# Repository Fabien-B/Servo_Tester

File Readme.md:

Servo Tester
=============

_This project is a work in progress. Some features are missing._

A device to quickly command servomoteurs and other stuff like I2C or CAN devices.

Based on a nucleo32 L432KC, this device allow to command up to 5 (only 3 working for now) classic servomotors.
It also support dynamixel AX-12A servomotors.

## Hardware

PCB was made with Kicad 5.0. Go to the Release page to get the gerbers files.

Run `git submodule update --init --recursive` to fetch kicad libraries.

## Software

The embedded firware uses ChibiOs.

For instructions about embedded firmware go to the appropriate [Readme file](software/embedded/Readme.md).

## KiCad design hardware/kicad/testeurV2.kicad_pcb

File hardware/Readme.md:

Tester hardware
================

The jumpers configuration on the NUCLEO L432KC needs to be changed: remove SB18, SB16 (for the I2C) and SB9 (to allow powering through 5V pin).

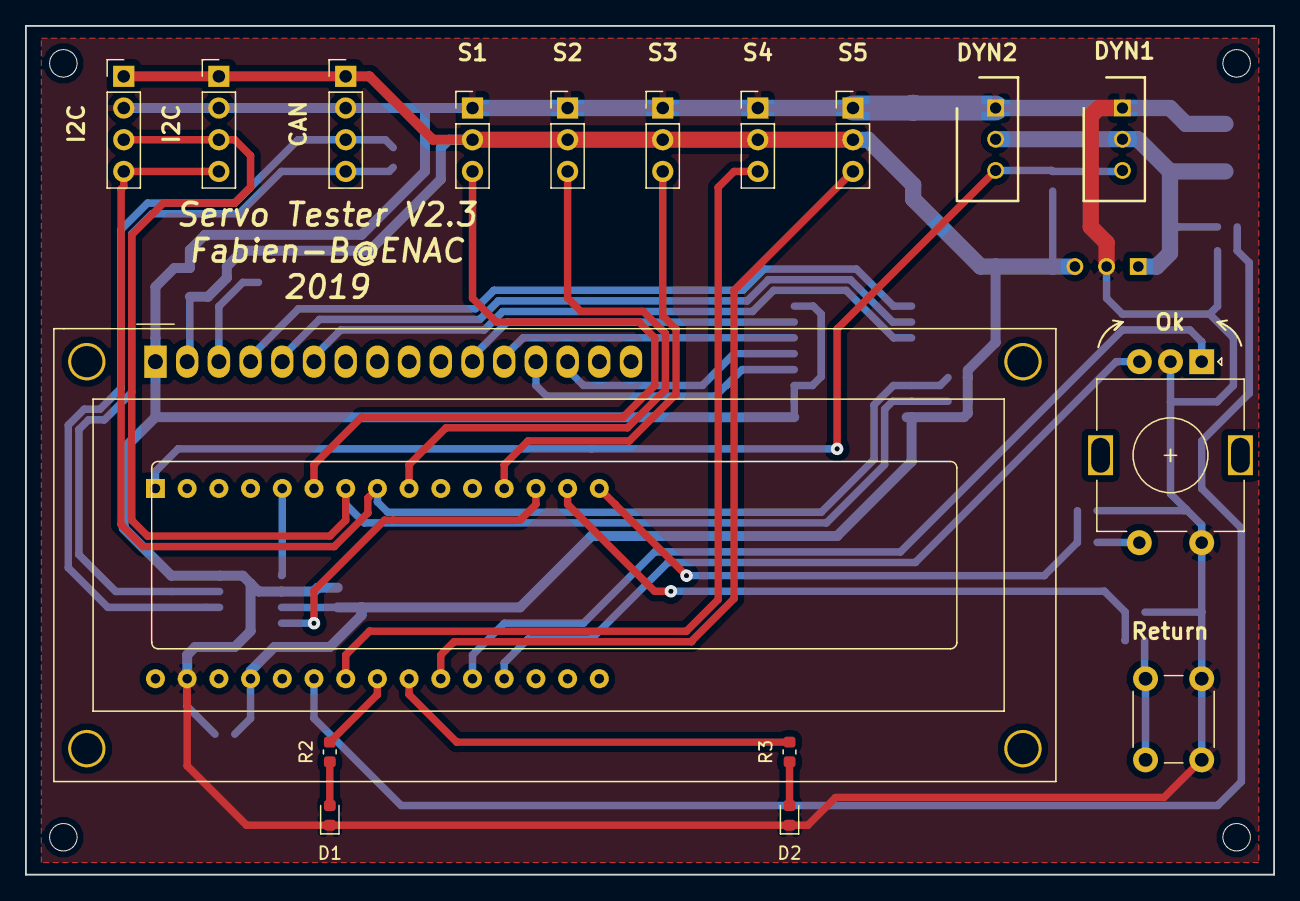
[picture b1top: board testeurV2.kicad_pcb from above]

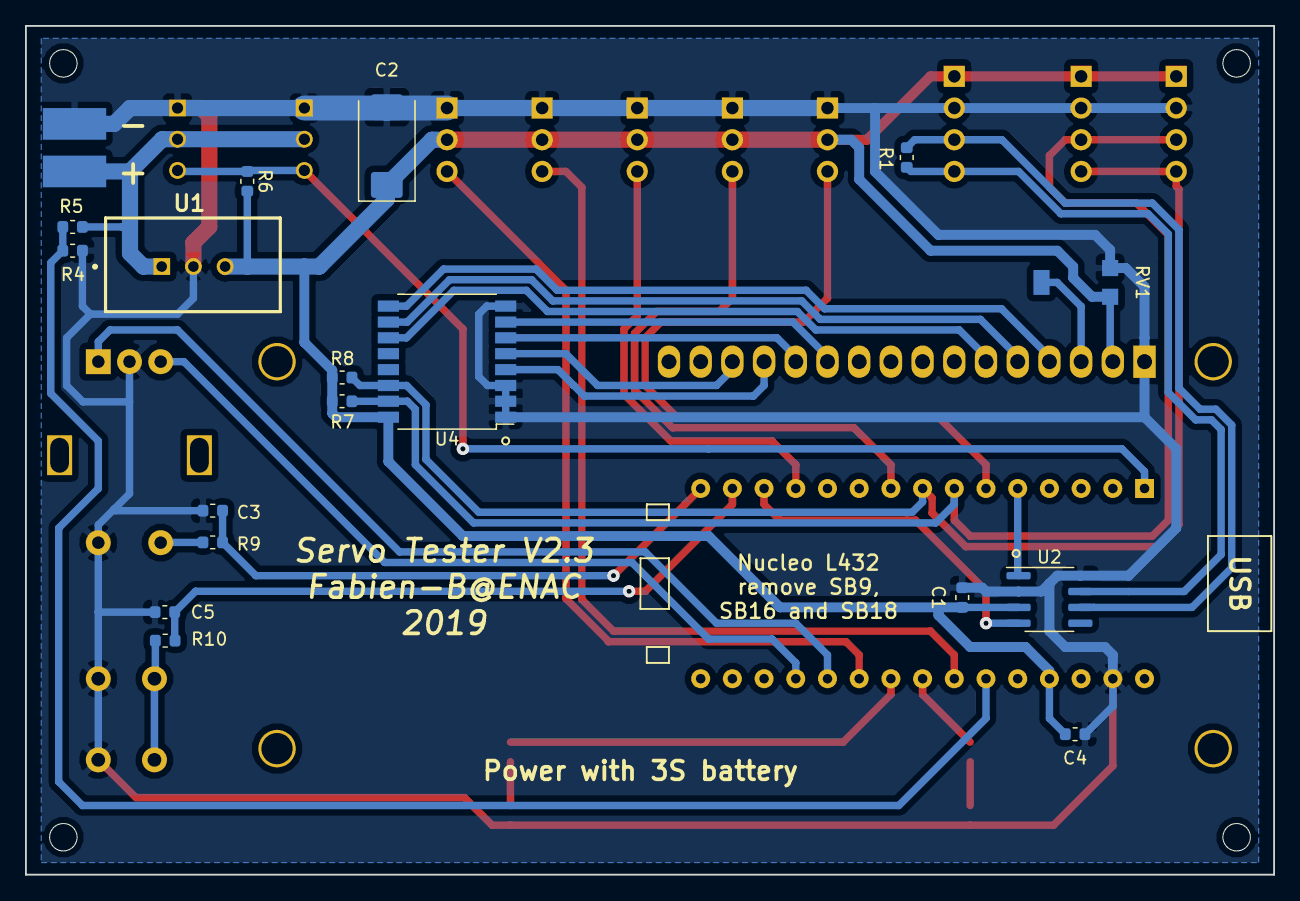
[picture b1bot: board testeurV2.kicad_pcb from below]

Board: 2 copper layers, 100.0 x 68.0 mm, 36 parts (19 on the bottom side), 34 nets.

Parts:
C1, C4: 100nF; C_0603_1608Metric
C2: 100µF; CP_EIA-7343-31_Kemet-D
C3, C5: 330nF; C_0603_1608Metric
CAN1: J_01x04P2.54; PinHeader_1x04_P2.54mm_Vertical
D1, D2: LED; LED_0603_1608Metric
DS1: WC1602A
DYN1, DYN2: 22-03-5035; SHDR3W70P0X250_1X3_990X490X590P
I2C1_a1, I2C1_b1: J_01x04P2.54; PinHeader_1x04_P2.54mm_Vertical
OK1: Rotary_Encoder_Switch; RotaryEncoder_Alps_EC11E-Switch_Vertical_H20mm
P1: Power_pads
R1: 120Ω; R_0603_1608Metric
R2, R3: 390Ω; R_0603_1608Metric
R4, R9, R10: 10k; R_0603_1608Metric
R5, R7, R8: 2.2k; R_0603_1608Metric
R6: 1k; R_0603_1608Metric
RV1: R_POT; TS53YL
Ret1: Push_Switch; SW_PUSH_6mm_H5mm
S1, S2, S3, S4, S5: JServo; PinHeader_1x03_P2.54mm_Vertical
U1: TSR_2-2450; TSR-2
U2: MCP2551-I-SN; SOIC-8_3.9x4.9mm_P1.27mm
U3: NUCLEO32-L432KC; NUCLEO32
U4: PCA9554D; SOP-16_7.5x10.4mm_P1.27mm

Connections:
+5V: C1.2, C2.1, C4.2, CAN1.1, DS1.2, I2C1_a1.1, I2C1_b1.1, R6.2, R7.1, R8.1, RV1.3, S1.2, S2.2, S3.2, S4.2, S5.2, U1.3, U2.3, U3.27, U4.16
+12V: DYN1.2, DYN2.2, P1.2, R4.1, U1.1
/BAT_MEAS: R4.2, R5.1, U3.25
/CAN_RX: U2.4, U3.13
/CAN_TX: U2.1, U3.5
/DYNAMIXEL: DYN1.3, DYN2.3, R6.1, U3.1
/ENC_A: OK1.A, U3.20
/ENC_B: OK1.B, U3.19
/I2C1_SCL: I2C1_a1.4, I2C1_b1.4, R8.2, U3.8, U4.14
/I2C1_SDA: I2C1_a1.3, I2C1_b1.3, R7.2, U3.7, U4.15
/OK_BTN: C3.1, R9.1, U3.15
/RET_BTN: C5.1, R10.1, U3.14
/SERVO1: S1.3, U3.6
/SERVO2: S2.3, U3.9
/SERVO3: S3.3, U3.12
/SERVO4: S4.3, U3.24
/SERVO5: S5.3, U3.21
GND: C1.1, C2.2, C3.2, C4.1, C5.2, CAN1.2, D1.1, D2.1, DS1.1, DYN1.1, DYN2.1, I2C1_a1.2, I2C1_b1.2, OK1.C, OK1.S2, P1.1, R5.2, RV1.1, Ret1.1, S1.1, S2.1, S3.1, S4.1, S5.1, U1.2, U2.2, U2.8, U3.29, U4.1, U4.2, U4.3, U4.8
unnamed: CAN1.3, R1.2, U2.6
unnamed: CAN1.4, R1.1, U2.7
unnamed: D1.2, R2.1
unnamed: D2.2, R3.1
unnamed: DS1.3, RV1.2
unnamed: DS1.4, U4.9
unnamed: DS1.5, U4.10
unnamed: DS1.6, U4.11
unnamed: DS1.11, U4.7
unnamed: DS1.12, U4.6
unnamed: DS1.13, U4.4
unnamed: DS1.14, U4.5
unnamed: OK1.S1, R9.2
unnamed: R2.2, U3.23
unnamed: R3.2, U3.22
unnamed: R10.2, Ret1.2

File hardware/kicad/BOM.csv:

Id,Référence,Boîtier,Quantité,Désignation,Fournisseur et réf,prix unitaire,total quantité
1,"S1,S2,S3,S4,S5",PinHeader_1x03_P2.54mm_Vertical,5,JServo,Usual 2.54mm pin header,"0,1","0,5"
2,"I2C1_a1,I2C1_b1,CAN1",PinHeader_1x04_P2.54mm_Vertical,3,J_01x04P2.54,Usual 2.54mm pin header,"0,1","0,3"
3,"DYN1,DYN2",SHDR3W70P0X250_1X3_990X490X590P,2,22-03-5035,https://fr.rs-online.com/web/p/embases-circuits-imprimes/6878048P/,"0,388","0,776"
4,"C1,C4",C_0603_1608Metric,2,100nF,,"0,1","0,2"
5,"C3,C5",C_0603_1608Metric,2,330nF,,"0,1","0,2"
6,C2,CP_EIA-7343-31_Kemet-D,1,100µF,https://fr.rs-online.com/web/p/condensateurs-tantale/6480402/,"0,403","0,403"
7,R1,R_0603_1608Metric,1,120Ω,,"0,1","0,1"
8,"R2,R3",R_0603_1608Metric,2,390Ω,,"0,1","0,2"
9,"R4,R9,R10",R_0603_1608Metric,3,10k,,"0,1","0,3"
10,"R5,R7,R8",R_0603_1608Metric,3,2.2k,,"0,1","0,3"
11,R6,R_0603_1608Metric,1,1k,,"0,1","0,1"
12,RV1,TS53YL,1,R_POT,https://fr.rs-online.com/web/p/trimmers/4867526/,"1,258","1,258"
13,"D1,D2",LED_0603_1608Metric,2,LED,,"0,1","0,2"
14,DS1,WC1602A,1,WC1602A,Standard LCD 16x2,6,6
15,Ret1,SW_PUSH_6mm_H5mm,1,Push_Switch,Dummy push switch,"0,1","0,1"
16,OK1,RotaryEncoder_Alps_EC11E-Switch_Vertical_H20mm,1,Rotary_Encoder_Switch,https://fr.rs-online.com/web/p/encodeurs-rotatifs-mecaniques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,"4,08","4,08"
17,U1,TSR-2,1,TSR_2-2450,https://fr.rs-online.com/web/p/regulateurs-a-decoupage/9068487/,"13,1","13,1"
18,U2,SOIC-8_3.9x4.9mm_P1.27mm,1,MCP2551-I-SN,https://fr.rs-online.com/web/p/transceivers-can/7386036/,"1,122","1,122"
19,U3,NUCLEO32,1,NUCLEO32-L432KC,https://fr.rs-online.com/web/p/kits-de-developpement-pour-pr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,"11,36","11,36"
20,U4,SOP-16_7.5x10.4mm_P1.27mm,1,PCA9554D,https://fr.rs-online.com/web/p/expandeurs-e-s/4837171/,"1,63","1,63"
,,,,,,,Total
,,,,,,,"42,229"

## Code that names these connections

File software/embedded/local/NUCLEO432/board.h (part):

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/*
 * IO pins assignments.
 */
#define	ENC_A                          0U
#define	ENC_B                          1U
#define	VCP_TX                         2U
#define	SERVO5                         3U
#define	LED1                           4U
#define	LED2                           5U
#define	SERVO4                         6U
#define	BAT_MEAS                       7U
#define	SERVO3                         8U
#define	TERMINAL_TX                    9U
#define	PA10                           10U
#define	CAN_RX                         11U
#define	CAN_TX                         12U
#define	SWDIO                          13U
#define	SWCLK                          14U
#define	VCP_RX                         15U

#define	SERVO1                         0U
#define	SERVO2                         1U
#define	PB02                           2U
#define	LED_GREEN                      3U
#define	OK_BTN                         4U
#define	RET_BTN                        5U
#define	SCL                            6U
#define	SDA                            7U
#define	PB08                           8U
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#define PIN_LOCKR_DISABLED(n)       (0U << (n))
#define PIN_LOCKR_ENABLED(n)        (1U << (n))

#define VAL_GPIOA_MODER                 (PIN_MODE_ALTERNATE(ENC_A) | \
					 PIN_MODE_ALTERNATE(ENC_B) | \
					 PIN_MODE_ALTERNATE(VCP_TX) | \
					 PIN_MODE_ALTERNATE(SERVO5) | \
					 PIN_MODE_OUTPUT(LED1) | \
					 PIN_MODE_OUTPUT(LED2) | \
					 PIN_MODE_ALTERNATE(SERVO4) | \
					 PIN_MODE_ANALOG(BAT_MEAS) | \
					 PIN_MODE_ALTERNATE(SERVO3) | \
					 PIN_MODE_ALTERNATE(TERMINAL_TX) | \
					 PIN_MODE_ANALOG(PA10) | \
					 PIN_MODE_ALTERNATE(CAN_RX) | \
					 PIN_MODE_ALTERNATE(CAN_TX) | \
					 PIN_MODE_ALTERNATE(SWDIO) | \
					 PIN_MODE_ALTERNATE(SWCLK) | \
					 PIN_MODE_ALTERNATE(VCP_RX))

#define VAL_GPIOA_OTYPER                (PIN_OTYPE_PUSHPULL(ENC_A) | \
					 PIN_OTYPE_PUSHPULL(ENC_B) | \
					 PIN_OTYPE_PUSHPULL(VCP_TX) | \
					 PIN_OTYPE_PUSHPULL(SERVO5) | \
					 PIN_OTYPE_PUSHPULL(LED1) | \
					 PIN_OTYPE_PUSHPULL(LED2) | \
					 PIN_OTYPE_PUSHPULL(SERVO4) | \
					 PIN_OTYPE_PUSHPULL(BAT_MEAS) | \
					 PIN_OTYPE_PUSHPULL(SERVO3) | \
					 PIN_OTYPE_PUSHPULL(TERMINAL_TX) | \
					 PIN_OTYPE_PUSHPULL(PA10) | \
					 PIN_OTYPE_PUSHPULL(CAN_RX) | \
					 PIN_OTYPE_PUSHPULL(CAN_TX) | \
					 PIN_OTYPE_PUSHPULL(SWDIO) | \
					 PIN_OTYPE_PUSHPULL(SWCLK) | \
					 PIN_OTYPE_PUSHPULL(VCP_RX))

#define VAL_GPIOA_OSPEEDR               (PIN_OSPEED_SPEED_HIGH(ENC_A) | \
					 PIN_OSPEED_SPEED_HIGH(ENC_B) | \
					 PIN_OSPEED_SPEED_HIGH(VCP_TX) | \
					 PIN_OSPEED_SPEED_HIGH(SERVO5) | \
					 PIN_OSPEED_SPEED_VERYLOW(LED1) | \
					 PIN_OSPEED_SPEED_VERYLOW(LED2) | \
					 PIN_OSPEED_SPEED_HIGH(SERVO4) | \
					 PIN_OSPEED_SPEED_VERYLOW(BAT_MEAS) | \
					 PIN_OSPEED_SPEED_HIGH(SERVO3) | \
					 PIN_OSPEED_SPEED_HIGH(TERMINAL_TX) | \
					 PIN_OSPEED_SPEED_VERYLOW(PA10) | \
					 PIN_OSPEED_SPEED_HIGH(CAN_RX) | \
					 PIN_OSPEED_SPEED_HIGH(CAN_TX) | \
					 PIN_OSPEED_SPEED_HIGH(SWDIO) | \
					 PIN_OSPEED_SPEED_HIGH(SWCLK) | \
					 PIN_OSPEED_SPEED_HIGH(VCP_RX))

#define VAL_GPIOA_PUPDR                 (PIN_PUPDR_PULLUP(ENC_A) | \
					 PIN_PUPDR_PULLUP(ENC_B) | \
					 PIN_PUPDR_FLOATING(VCP_TX) | \
					 PIN_PUPDR_FLOATING(SERVO5) | \
					 PIN_PUPDR_FLOATING(LED1) | \
					 PIN_PUPDR_FLOATING(LED2) | \
					 PIN_PUPDR_FLOATING(SERVO4) | \
					 PIN_PUPDR_FLOATING(BAT_MEAS) | \
					 PIN_PUPDR_FLOATING(SERVO3) | \
					 PIN_PUPDR_FLOATING(TERMINAL_TX) | \
					 PIN_PUPDR_FLOATING(PA10) | \
					 PIN_PUPDR_FLOATING(CAN_RX) | \
					 PIN_PUPDR_FLOATING(CAN_TX) | \
					 PIN_PUPDR_PULLUP(SWDIO) | \
					 PIN_PUPDR_PULLUP(SWCLK) | \
					 PIN_PUPDR_FLOATING(VCP_RX))

#define VAL_GPIOA_ODR                   (PIN_ODR_LEVEL_HIGH(ENC_A) | \
					 PIN_ODR_LEVEL_HIGH(ENC_B) | \
					 PIN_ODR_LEVEL_HIGH(VCP_TX) | \
					 PIN_ODR_LEVEL_LOW(SERVO5) | \
					 PIN_ODR_LEVEL_LOW(LED1) | \
					 PIN_ODR_LEVEL_LOW(LED2) | \
					 PIN_ODR_LEVEL_LOW(SERVO4) | \
					 PIN_ODR_LEVEL_LOW(BAT_MEAS) | \
					 PIN_ODR_LEVEL_LOW(SERVO3) | \
					 PIN_ODR_LEVEL_HIGH(TERMINAL_TX) | \
					 PIN_ODR_LEVEL_HIGH(PA10) | \
					 PIN_ODR_LEVEL_HIGH(CAN_RX) | \
					 PIN_ODR_LEVEL_HIGH(CAN_TX) | \
					 PIN_ODR_LEVEL_HIGH(SWDIO) | \
					 PIN_ODR_LEVEL_HIGH(SWCLK) | \
					 PIN_ODR_LEVEL_HIGH(VCP_RX))

#define VAL_GPIOA_AFRL			(PIN_AFIO_AF(ENC_A, 1) | \
					 PIN_AFIO_AF(ENC_B, 1) | \
					 PIN_AFIO_AF(VCP_TX, 7) | \
					 PIN_AFIO_AF(SERVO5, 1) | \
					 PIN_AFIO_AF(LED1, 0) | \
					 PIN_AFIO_AF(LED2, 0) | \
					 PIN_AFIO_AF(SERVO4, 14) | \
					 PIN_AFIO_AF(BAT_MEAS, 0))

#define VAL_GPIOA_AFRH			(PIN_AFIO_AF(SERVO3, 1) | \
					 PIN_AFIO_AF(TERMINAL_TX, 7) | \
					 PIN_AFIO_AF(PA10, 0) | \
					 PIN_AFIO_AF(CAN_RX, 9) | \
					 PIN_AFIO_AF(CAN_TX, 9) | \
					 PIN_AFIO_AF(SWDIO, 0) | \
					 PIN_AFIO_AF(SWCLK, 0) | \
					 PIN_AFIO_AF(VCP_RX, 3))

#define VAL_GPIOA_ASCR                  (PIN_ASCR_DISABLED(ENC_A) | \
					 PIN_ASCR_DISABLED(ENC_B) | \
					 PIN_ASCR_DISABLED(VCP_TX) | \
					 PIN_ASCR_DISABLED(SERVO5) | \
					 PIN_ASCR_DISABLED(LED1) | \
					 PIN_ASCR_DISABLED(LED2) | \
					 PIN_ASCR_DISABLED(SERVO4) | \
					 PIN_ASCR_ENABLED(BAT_MEAS) | \
					 PIN_ASCR_DISABLED(SERVO3) | \
					 PIN_ASCR_DISABLED(TERMINAL_TX) | \
					 PIN_ASCR_DISABLED(PA10) | \
					 PIN_ASCR_DISABLED(CAN_RX) | \
					 PIN_ASCR_DISABLED(CAN_TX) | \
					 PIN_ASCR_DISABLED(SWDIO) | \
					 PIN_ASCR_DISABLED(SWCLK) | \
					 PIN_ASCR_DISABLED(VCP_RX))

#define VAL_GPIOA_LOCKR                 (PIN_LOCKR_DISABLED(ENC_A) | \
					 PIN_LOCKR_DISABLED(ENC_B) | \
					 PIN_LOCKR_DISABLED(VCP_TX) | \
					 PIN_LOCKR_DISABLED(SERVO5) | \
					 PIN_LOCKR_DISABLED(LED1) | \
					 PIN_LOCKR_DISABLED(LED2) | \
					 PIN_LOCKR_DISABLED(SERVO4) | \
					 PIN_LOCKR_DISABLED(BAT_MEAS) | \
					 PIN_LOCKR_DISABLED(SERVO3) | \
					 PIN_LOCKR_DISABLED(TERMINAL_TX) | \
					 PIN_LOCKR_DISABLED(PA10) | \
					 PIN_LOCKR_DISABLED(CAN_RX) | \
					 PIN_LOCKR_DISABLED(CAN_TX) | \
					 PIN_LOCKR_DISABLED(SWDIO) | \
					 PIN_LOCKR_DISABLED(SWCLK) | \
					 PIN_LOCKR_DISABLED(VCP_RX))

#define VAL_GPIOB_MODER                 (PIN_MODE_ALTERNATE(SERVO1) | \
					 PIN_MODE_ALTERNATE(SERVO2) | \
					 PIN_MODE_ANALOG(PB02) | \
					 PIN_MODE_OUTPUT(LED_GREEN) | \
					 PIN_MODE_INPUT(OK_BTN) | \
					 PIN_MODE_INPUT(RET_BTN) | \
					 PIN_MODE_ALTERNATE(SCL) | \
					 PIN_MODE_ALTERNATE(SDA) | \
					 PIN_MODE_ANALOG(PB08) | \
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					 PIN_MODE_ANALOG(PB14) | \
					 PIN_MODE_ANALOG(PB15))

#define VAL_GPIOB_OTYPER                (PIN_OTYPE_PUSHPULL(SERVO1) | \
					 PIN_OTYPE_PUSHPULL(SERVO2) | \
					 PIN_OTYPE_PUSHPULL(PB02) | \
					 PIN_OTYPE_PUSHPULL(LED_GREEN) | \
					 PIN_OTYPE_OPENDRAIN(OK_BTN) | \
					 PIN_OTYPE_OPENDRAIN(RET_BTN) | \
					 PIN_OTYPE_OPENDRAIN(SCL) | \
					 PIN_OTYPE_OPENDRAIN(SDA) | \
					 PIN_OTYPE_PUSHPULL(PB08) | \
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					 PIN_OTYPE_PUSHPULL(PB14) | \
					 PIN_OTYPE_PUSHPULL(PB15))

#define VAL_GPIOB_OSPEEDR               (PIN_OSPEED_SPEED_HIGH(SERVO1) | \
					 PIN_OSPEED_SPEED_HIGH(SERVO2) | \
					 PIN_OSPEED_SPEED_VERYLOW(PB02) | \
					 PIN_OSPEED_SPEED_VERYLOW(LED_GREEN) | \
					 PIN_OSPEED_SPEED_VERYLOW(OK_BTN) | \
					 PIN_OSPEED_SPEED_VERYLOW(RET_BTN) | \
					 PIN_OSPEED_SPEED_HIGH(SCL) | \
					 PIN_OSPEED_SPEED_HIGH(SDA) | \
					 PIN_OSPEED_SPEED_VERYLOW(PB08) | \
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					 PIN_OSPEED_SPEED_VERYLOW(PB14) | \
					 PIN_OSPEED_SPEED_VERYLOW(PB15))

#define VAL_GPIOB_PUPDR                 (PIN_PUPDR_FLOATING(SERVO1) | \
					 PIN_PUPDR_FLOATING(SERVO2) | \
					 PIN_PUPDR_FLOATING(PB02) | \
					 PIN_PUPDR_FLOATING(LED_GREEN) | \
					 PIN_PUPDR_PULLUP(OK_BTN) | \
					 PIN_PUPDR_PULLUP(RET_BTN) | \
					 PIN_PUPDR_PULLUP(SCL) | \
					 PIN_PUPDR_PULLUP(SDA) | \
					 PIN_PUPDR_FLOATING(PB08) | \
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					 PIN_PUPDR_FLOATING(PB14) | \
					 PIN_PUPDR_FLOATING(PB15))

#define VAL_GPIOB_ODR                   (PIN_ODR_LEVEL_LOW(SERVO1) | \
					 PIN_ODR_LEVEL_LOW(SERVO2) | \
					 PIN_ODR_LEVEL_HIGH(PB02) | \
					 PIN_ODR_LEVEL_LOW(LED_GREEN) | \
					 PIN_ODR_LEVEL_LOW(OK_BTN) | \
					 PIN_ODR_LEVEL_LOW(RET_BTN) | \
					 PIN_ODR_LEVEL_HIGH(SCL) | \
					 PIN_ODR_LEVEL_HIGH(SDA) | \
					 PIN_ODR_LEVEL_HIGH(PB08) | \
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					 PIN_ODR_LEVEL_HIGH(PB14) | \
					 PIN_ODR_LEVEL_HIGH(PB15))

#define VAL_GPIOB_AFRL			(PIN_AFIO_AF(SERVO1, 1) | \
					 PIN_AFIO_AF(SERVO2, 1) | \
					 PIN_AFIO_AF(PB02, 0) | \
					 PIN_AFIO_AF(LED_GREEN, 0) | \
					 PIN_AFIO_AF(OK_BTN, 0) | \
					 PIN_AFIO_AF(RET_BTN, 0) | \
					 PIN_AFIO_AF(SCL, 4) | \
					 PIN_AFIO_AF(SDA, 4))

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					 PIN_AFIO_AF(PB14, 0) | \
					 PIN_AFIO_AF(PB15, 0))

#define VAL_GPIOB_ASCR                  (PIN_ASCR_DISABLED(SERVO1) | \
					 PIN_ASCR_DISABLED(SERVO2) | \
					 PIN_ASCR_DISABLED(PB02) | \
					 PIN_ASCR_DISABLED(LED_GREEN) | \
					 PIN_ASCR_DISABLED(OK_BTN) | \
					 PIN_ASCR_DISABLED(RET_BTN) | \
					 PIN_ASCR_DISABLED(SCL) | \
					 PIN_ASCR_DISABLED(SDA) | \
					 PIN_ASCR_DISABLED(PB08) | \
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					 PIN_ASCR_DISABLED(PB14) | \
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
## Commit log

2019-06-14 InitialCommit
2019-06-14 Adds library as submodule
2019-06-14 Update libraries.
2019-06-14 Adds schematics.
2019-06-16 Assigns footprints.
2019-06-16 convenience edits.
2019-06-16 components placing.
2019-06-17 testeurV2 R0.1
2019-06-19 Adds pullup for dynamixels.
2019-09-12 Adds MAX6818 to debounce buttons. Adds missing pullup on dynamixel UART.
2019-09-12 Change directory tree. Adds I2C pullups.
2019-09-12 Adds datasheets.
2019-09-12 Adds Readme.
2019-09-15 Reconfigure libs submodule.
2019-09-16 Adds 2nd board version.
2019-10-11 [1st Firmware] Adds first firmware version. Features servo moves, Dynamixel move, setId, endless mode.
2019-10-11 [Harware] Update to last version.
2019-10-29 Fix hardware and move to V2.3.
2019-11-19 Rename file + change some part names.
2019-11-19 Adds component cost estimation.
2019-11-19 Removes old file and rename kicad files.
2019-12-01 Adds ChibiOs and some tools as submodules
2019-12-01 Adds some datasheets.
2019-12-03 Uses hardware encoders.
2019-12-03 Add sleep to release CPU.
2019-12-03 Adds VSCode tasks and debugging configuration.
2019-12-03 Adds gitignore
2019-12-03 Adds udev rule for black magic probe.
2019-12-03 Add instructions about udev rules for black magic probe.
2019-12-03 [Actions] Adds ARM autobuild test
2019-12-03 [Actions] Updates README
2019-12-03 Remove board.h
2019-12-04 Add SRF02 driver.
2019-12-05 Adds VL6180x driver.
2019-12-05 Adds missing dependencies and fix typo.
2020-04-26 Handle dynamixel move via serial interface.
2023-06-20 Set Dynamixel TX as push-pull. In half-duplex, TX is push-pull during a transaction, and Hi-Z otherwise.
2024-02-14 Add dynamixel "dyn" command.

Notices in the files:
software/embedded/local/NUCLEO432/board.h:
ChibiOS - Copyright (C) 2006..2015 Giovanni Di Sirio
Licensed under the Apache License, Version 2.0 (the "License");
